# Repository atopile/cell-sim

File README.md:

# Cell Simulator

This cell-sim is designed to mimic a LiPo battery pack for development of surrounding electronics (e.g. a BMS).

- 16 channels
- Open-Source hardware design, you can embed onto your own HIL setup
- ⚡️ 0-4.5V and 0-500mA per channel
- DMM muxed to each channel for arbitrarily precise measurement
- Open-circuit (open-wire) simulation on each channel
- 📏 16bit ADC feedback for voltage and current
- 🔌 USB w/ Python software interface (+ 100MBit Ethernet + WiFi waiting for firmware support)

## Documentation

- **Electronics**: this README (see diagrams below)
- **Software (firmware + Python)**: `SOFTWARE.md`

## Design overview

## How it works (electronics)

### System-level overview

```mermaid
flowchart TB
  %% ----------------------------
  %% Power tree
  %% ----------------------------
  subgraph PWR["Power tree"]
    XT30["XT30 input<br/>12-20V"] --> PI["Pi filter"] --> ISENSE["Input current sensor"] --> VIN["POWER_IN<br/>12-20V rail"]
    VIN --> BUCK5["LV2842X buck<br/>12-20V to 5V"]
    USBC["USB-C"] -->|VBUS 5V| OR["Diode OR-ing"]
    BUCK5 --> OR --> P5V["5V rail"]
    P5V --> LDO33["LDK220 LDO<br/>5V to 3.3V"] --> P3V3["3.3V rail"]
  end

  %% ----------------------------
  %% Controller + comms
  %% ----------------------------
  subgraph MCU["Controller + comms"]
    ESP["ESP32-S3"]:::mcu
    P3V3 --> ESP
    USBC -->|USB2 data| ESP

    ESP -->|I2C bus #1| I2C1["I2C1"]
    ESP -->|I2C bus #2| I2C2["I2C2"]

    I2C1 --> MUX1["TCA9548A #1<br/>addr 0x70"]
    I2C2 --> MUX2["TCA9548A #2<br/>addr 0x70"]
    P3V3 --> MUX1
    P3V3 --> MUX2

    ESP -->|SPI| W5500["W5500 Ethernet<br/>hw present; fw WIP"]
    P3V3 --> W5500
  end

  %% ----------------------------
  %% 16 cell channels (stacked)
  %% ----------------------------
  subgraph STACK["16x isolated cell channels<br/>stacked like a battery pack"]
    direction TB
    C1["Cell #1<br/>pack GND reference"] --> C2["Cell #2"] --> C3["Cell #3"] --> C4["Cell #4"] --> C5["Cell #5"] --> C6["Cell #6"] --> C7["Cell #7"] --> C8["Cell #8"]
    C8 --> C9["Cell #9"] --> C10["Cell #10"] --> C11["Cell #11"] --> C12["Cell #12"] --> C13["Cell #13"] --> C14["Cell #14"] --> C15["Cell #15"] --> C16["Cell #16<br/>pack +"]
  end

  %% Per-cell services fed from global rails
  VIN -->|12-20V feed| STACK
  P5V -->|logic / relay / LED feed| STACK
  P3V3 -->|isolator side power| STACK

  %% I2C fanout
  MUX1 -->|ports 0-7 to cells 1-8| C1
  MUX2 -->|ports 0-7 to cells 9-16| C9

  %% ----------------------------
  %% DMM path (precision external measurement)
  %% ----------------------------
  subgraph DMM["External DMM measurement path"]
    BANANA["Banana jacks<br/>DMM connector"] --> DMMBUS["DMM_OUT bus"]

    ESP -->|S0..S3 + /EN| DMMSW["CD74HC4067<br/>16:1 mux"]
    P3V3 -->|3.3V select level| DMMSW
    DMMSW -->|CH0..CH15 -> per-cell dmm_relay_enable| STACK

    STACK -->|selected cell closes DMM relay, routes output to DMM_OUT| DMMBUS
  end

  %% ----------------------------
  %% Thermistor simulator
  %% ----------------------------
  subgraph THERM["4x digital thermistor simulator"]
    TSIM["Isolated thermistor simulator<br/>MCP4728 DAC + ADS1115 ADC"] -->|4 analog thermistor nodes| THOUT["thermistor outputs"]
    I2C2 -->|I2C control| TSIM
    VIN -->|12-20V| TSIM
    P3V3 -->|logic-side isolator power| TSIM
  end

  classDef mcu fill:#eef,stroke:#446;
```

### What a single cell channel does internally

Each channel is effectively an *isolated, digitally-controlled power supply* whose output is treated like a single LiPo cell. The channels are then wired in series to create a 16S “battery pack” at the output connector.

```mermaid
flowchart LR
  %% One "Cell" module from elec/src/cell.ato
  subgraph CELL["One cell channel<br/>isolated"]
    direction LR

    %% Power path (high-level)
    VIN["POWER_IN<br/>12-20V"] --> ISO_DCDC["Isolated DC/DC<br/>B1205S"] --> ISO5V["Isolated 5V"]
    ISO5V --> INTLDO["Local LDO<br/>5V to 3.3V"] --> ISO3V3["Isolated 3.3V<br/>logic"]

    ISO5V --> DBUCK["Digitally-controlled buck"] --> DLDO["Digitally-controlled LDO"] --> PF["Pi filter"] --> CS["Current sense"] --> OUTRELAY["Output relay"] --> VOUT["Cell output"]

    %% Control + monitoring (isolated I2C domain)
    I2C_IN["I2C from mux port"] --> ISOI2C["ISO1640 I2C isolator"] --> I2C_ISO["I2C isolated"]
    ISO3V3 --> ISOI2C

    I2C_ISO --> DACB["DAC @0x61<br/>buck setpoint"]
    I2C_ISO --> DACL["DAC @0x60<br/>LDO setpoint"]
    I2C_ISO --> ADC["ADS1115 @0x48<br/>telemetry"]
    I2C_ISO --> GPIO["TCA6408 @0x20<br/>GPIO expander"]
    I2C_ISO --> ISENSE_IC["Current sense IC @0x21"]

    GPIO -->|enable| DBUCK
    GPIO -->|enable| DLDO
    GPIO -->|control| LOADSW["Load switch"]
    GPIO -->|control| OUTRELAY

    %% Telemetry points
    ADC -->|buck V| DBUCK
    ADC -->|LDO V| DLDO
    ADC -->|output V| VOUT
    ADC -->|shunt V| CS

    %% Fast discharge path
    PF --> LOADSW --> RLOAD["Discharge resistor"] --> PF

    %% Precision measurement path (selected externally)
    CS --> DMMRELAY["DMM relay"] --> RLIM["Current-limiting resistors"] --> DMM_OUT["DMM_OUT bus"]
  end
```

## Getting Started

1. Install python if you don't have it already
2. Install the requirements `pip install -r requirements.txt`
3. Connect the board via USB

4. Power the board with the 12V input (supply: 1A minimum, 3A recommended)
5. Run the example python script `python example_set_voltages.py`
6. Voltages should be set to 3.5V, then rainbow from 1V to 4V across the 16 channels and current should be close to 0A.

You should see something like this:

## Notes
1. To get best low noise performance, use a quality power supply for the input supply.

## Manufacturing
Board is intended to be manufactured with JLC, files are in the main directory of the repository.
Note, the highlighted isolated regulator needs to be depopulated:

## Firmware

### Update Firmware
We use PlatformIO to build and upload the firmware via USB.
1. Install PlatformIO: https://platformio.org/install
2. Connect the board via USB (might need to accept connection popup on Mac)
3. Run `pio run -t upload` or install the PlatformIO VSCode extension and use the upload button.

See `SOFTWARE.md` for firmware architecture, protocol, and troubleshooting.

## API Docs
### Connecting to cellsim

```python
from lib.cellsim import CellSim
cellsim = CellSim(port)
```

### Enable outputs
Each cell has a relay in series between the cell output and the connector, this can be  used to simulate open-wire faults for example.

```python
# Global enable/disable
cellsim.enableOutputAll()
time.sleep(1)
cellsim.disableOutputAll()
time.sleep(1)

# Enable/disable one at a time
# Turn relays on in a wave
for i in range(1, 17):
    cellsim.enableOutput(i)
    time.sleep(0.1)

time.sleep(1)

# Turn relays off in a wave
for i in range(1, 17):
    cellsim.disableOutput(i)
    time.sleep(0.1)
```

### Setting voltages
Each output voltage can be specified between 0.5V and 4.4V

```python
# Set all at once
cellsim.setAllVoltages(3.5)
time.sleep(1)

# Set one at a time
print("\nSetting rainbow voltage pattern...")
for i in range(16):
    voltage = 1.0 + (3.0 * i / 15)  # Spread 1V to 4V across 16 channels
    cellsim.setVoltage(i + 1, voltage)
```

### Measuring voltages (onboard)
Each channel has an onboard 16bit ADC that measures the cell output. Note this is not a kelvin connection to your DUT, the measurement will only be accurate when minimal current is being drawn by the DUT.

```python
voltages = cellsim.getAllVoltages()
print(f"Voltages: {[f'{v:.3f}' for v in voltages]}")
```
  
### Measuring voltages externally
To take a precision measurement, each channel has a multiplexed output that connects to the DMM connector via a relay.

```python
channel_to_measure = 3
# Enable DMM
cellsim.enableDMM(channel_to_measure)

# take measurment using external DMM
# that is connected to the DMM banana outputs
time.sleep(1)

cellsim.disableDMM()
```

### Load switch
Each channel has a resistor + mosfet across its output, this can be used to speed up the discharge of the output capacitors. For example when transitioning from a high output voltage to a low output voltage, there will be an RC decay time before the voltage settles, typically in the ~100ms range. Turning on the load switch will make this much faster.

```python
cellsim.enableLoadSwitchAll()
time.sleep(1)

cellsim.disableLoadSwitchAll()
time.sleep(1)
```

### Disconnecting session
Once your test is finished, you can use the following to close the serial session:
```python
  cellsim.close()
```

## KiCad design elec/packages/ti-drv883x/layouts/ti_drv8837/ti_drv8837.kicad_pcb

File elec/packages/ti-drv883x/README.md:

# Texas Instruments DRV8837/DRV8838 H-Bridge Motor Drivers

Low-voltage H-bridge motor drivers for brushed DC motors.

- **DRV8837**: IN0/IN1 control interface
- **DRV8838**: PH/EN (Phase/Enable) control interface

## Features

- Logic voltage: 1.8V to 7V
- Motor voltage: 0V to 11V
- Integrated decoupling capacitors
- Sleep control for low-power mode

## Usage

```ato
#pragma experiment("TRAITS")
#pragma experiment("BRIDGE_CONNECT")
#pragma experiment("MODULE_TEMPLATING")

import ElectricPower
import ElectricLogic
import Electrical
import can_bridge_by_name

from "atopile/ti-drv883x/ti-drv883x.ato" import TI_DRV8837
from "atopile/ti-drv883x/ti-drv883x.ato" import TI_DRV8838

module FakeMotor:
    """
    Mock motor device for testing
    """
    unnamed = new Electrical[2]
    trait can_bridge_by_name<input_name = "unnamed[0]", output_name = "unnamed[1]">

module Usage:
    """
    Example usage of the TI_DRV8837 and TI_DRV8838 H-bridge (motor) drivers
    """

    power_3v3 = new ElectricPower
    power_3v3.voltage = 3.3V +/- 5%
    power_6v = new ElectricPower
    power_6v.voltage = 6V +/- 5%

    # some mock gpio from e.g. a gpio expander
    gpio_0 = new ElectricLogic
    gpio_1 = new ElectricLogic
    gpio_3 = new ElectricLogic

    motor_driver_in0_in1 = new TI_DRV8837
    motor_driver_in0_in1.logic_power ~ power_3v3
    motor_driver_in0_in1.motor_power ~ power_6v
    motor_driver_in0_in1.sleep ~ gpio_3
    motor_driver_in0_in1.inputs[0] ~ gpio_0
    motor_driver_in0_in1.inputs[1] ~ gpio_1
    motor_0 = new FakeMotor
    motor_driver_in0_in1.motor_outs[0] ~> motor_0 ~> motor_driver_in0_in1.motor_outs[1]

    motor_driver_ph_en = new TI_DRV8838
    motor_driver_ph_en.logic_power ~ power_3v3
    motor_driver_ph_en.motor_power ~ power_6v
    motor_driver_ph_en.sleep ~ gpio_3
    motor_driver_ph_en.phase ~ gpio_0
    motor_driver_ph_en.enable ~ gpio_1
    motor_1 = new FakeMotor
    motor_driver_ph_en.motor_outs[0] ~> motor_1 ~> motor_driver_ph_en.motor_outs[1]

```

### DRV8837 Truth Table (IN0/IN1)

| nSLEEP | IN1 | IN2 | OUT1 | OUT2 | Function |
| ------ | --- | --- | ---- | ---- | -------- |
| 0      | X   | X   | Z    | Z    | Coast    |
| 1      | 0   | 0   | Z    | Z    | Coast    |
| 1      | 0   | 1   | L    | H    | Reverse  |
| 1      | 1   | 0   | H    | L    | Forward  |
| 1      | 1   | 1   | L    | L    | Brake    |

### DRV8838 Truth Table (PH/EN)

| nSLEEP | PH  | EN  | OUT1 | OUT2 | Function |
| ------ | --- | --- | ---- | ---- | -------- |
| 0      | X   | X   | Z    | Z    | Coast    |
| 1      | X   | 0   | L    | L    | Brake    |
| 1      | 1   | 1   | L    | H    | Reverse  |
| 1      | 0   | 1   | H    | L    | Forward  |

## Contributing

Contributions to this package are welcome via pull requests on the GitHub repository.

## License

This atopile package is provided under the [MIT License](https://opensource.org/license/mit/).

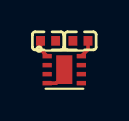
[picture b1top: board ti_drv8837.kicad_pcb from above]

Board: 2 copper layers, 3 parts (0 on the bottom side), 3 nets.

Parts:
C1, C2: 100nF; C0402
U1: WSON-8_L2.0-W2.0-P0.50-TL-EP

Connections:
hv: C1.1, U1.8
lv: C1.2, C2.2, U1.4, U1.9
motor_power_decoupling_capacitor-power-hv: C2.1, U1.1

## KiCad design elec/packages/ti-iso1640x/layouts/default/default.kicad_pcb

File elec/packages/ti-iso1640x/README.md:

# Texas Instruments ISO1640QDWRQ1 Bidirectional I2C Isolator

The ISO1640QDWRQ1 is a bidirectional I2C isolator that provides 1500V isolation between two I2C buses. It supports data rates up to 1MHz and operates with supply voltages from 2.25V to 5.5V on each side. This device is automotive qualified (AEC-Q100).

## Usage

```ato
import I2C
import ElectricPower

from "atopile/ti-iso1640x/ti-iso1640x.ato" import TI_ISO1640QDWRQ1

module Usage:
    """
    Example usage of ISO1640QDWRQ1 I2C isolator
    """

    isolator = new TI_ISO1640QDWRQ1

    power_3v3 = new ElectricPower
    power_iso_3v3 = new ElectricPower

    assert power_3v3.voltage within 3.3V +/- 5%
    assert power_iso_3v3.voltage within 3.3V +/- 5%

    i2c_mcu = new I2C
    i2c_sensor = new I2C

    assert i2c_mcu.frequency <= 400kHz
    assert i2c_sensor.frequency <= 400kHz

    # Connections
    i2c_mcu ~ isolator.i2cs[0]
    i2c_sensor ~ isolator.i2cs[1]
    power_3v3 ~ isolator.power_rails[0]
    power_iso_3v3 ~ isolator.power_rails[1]
```

## Contributing

Contributions are welcome! Feel free to open issues or pull requests.

## License

This package is provided under the [MIT License](https://opensource.org/license/mit/).

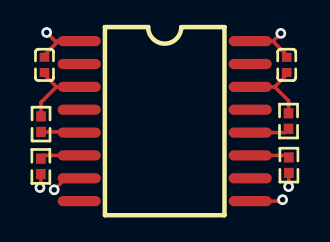
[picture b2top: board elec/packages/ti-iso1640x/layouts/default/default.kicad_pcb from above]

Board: 2 copper layers, 7 parts (0 on the bottom side), 6 nets.

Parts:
C1, C2: 100nF; C0402
R1, R2, R3, R4: 10kΩ; R0402
U1: SOIC-16_L10.3-W7.4-P1.27-LS10.3-BL

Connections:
SCL: R1.2, R2.2, U1.6, U1.11
SDA: R3.2, R4.2, U1.5, U1.12
decoupling_cap_side2-power-hv: C2.1, R2.1, R4.1, U1.14
decoupling_cap_side2-power-lv: C2.2, U1.9, U1.16
hv: C1.1, R1.1, R3.1, U1.3
lv: C1.2, U1.1, U1.7

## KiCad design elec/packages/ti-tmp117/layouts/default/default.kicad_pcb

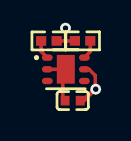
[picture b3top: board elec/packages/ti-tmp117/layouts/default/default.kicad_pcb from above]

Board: 2 copper layers, 4 parts (0 on the bottom side), 4 nets.

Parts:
C1: 100nF; C0402
R1, R2: 10kΩ; R0402
U1: WSON-6_L2.0-W2.0-P0.65-TL-EP

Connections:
SCL: R1.1, U1.1
SDA: R2.1, U1.6
hv: C1.1, R1.2, R2.2, U1.5
lv: C1.2, U1.2, U1.4, U1.7

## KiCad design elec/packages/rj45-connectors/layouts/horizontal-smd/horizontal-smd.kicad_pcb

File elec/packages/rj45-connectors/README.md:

# RJ45 Connectors

## Usage

```ato
#pragma experiment("BRIDGE_CONNECT")
#pragma experiment("FOR_LOOP")
#pragma experiment("TRAITS")

import Electrical
import ElectricLogic
import ElectricPower
import Ethernet

from "atopile/rj45-connectors/rj45-connectors.ato" import RJ45_Vertical_SMD
from "atopile/rj45-connectors/rj45-connectors.ato" import RJ45_Horizontal_TH_Magnetics
from "atopile/rj45-connectors/rj45-connectors.ato" import RJ45_Recessed_SMD
from "atopile/rj45-connectors/rj45-connectors.ato" import RJ45_Horizontal_TH_Magnetics_8Port
from "atopile/rj45-connectors/rj45-connectors.ato" import RJ45_Horizontal_SMD_Magnetics

module Usage:
    """
    Usage examples for RJ45 connectors package.

    Shows how to use both the vertical SMD connector (without magnetics)
    and the horizontal through-hole connector (with integrated magnetics).
    """

    # --- Power supply for logic references ---
    power_3v3 = new ElectricPower
    assert power_3v3.voltage within 3.3V +/- 5%

    # --- Example 1: Vertical SMD connector (no magnetics) ---
    rj45_vertical = new RJ45_Vertical_SMD

    # Connect Ethernet interface power reference
    rj45_vertical.ethernet.led_link.reference ~ power_3v3
    rj45_vertical.ethernet.led_speed.reference ~ power_3v3

    # Connect shield to ground
    rj45_vertical.shield ~ power_3v3.lv

    # --- Example 2: Horizontal TH connector with magnetics ---
    rj45_horizontal = new RJ45_Horizontal_TH_Magnetics

    # Connect Ethernet interface power reference
    rj45_horizontal.ethernet.led_link.reference ~ power_3v3
    rj45_horizontal.ethernet.led_speed.reference ~ power_3v3

    # Connect shield to ground
    rj45_horizontal.shield ~ power_3v3.lv

    # --- Example 3: Horizontal SMD connector with magnetics (HCTL HC632701A-M906-A) ---
    rj45_horizontal_smd = new RJ45_Horizontal_SMD_Magnetics
    rj45_horizontal_smd.ethernet.led_link.reference ~ power_3v3
    rj45_horizontal_smd.ethernet.led_speed.reference ~ power_3v3
    rj45_horizontal_smd.shield ~ power_3v3.lv

    # --- Example connections to external circuits ---
    # For the magnetics connector, you can connect directly to an Ethernet PHY:
    # phy.ethernet ~ rj45_horizontal.ethernet
    # For the vertical SMD, you would typically need external transformers

    rj45_recessed = new RJ45_Recessed_SMD
    rj45_recessed.ethernet.led_link.reference ~ power_3v3
    rj45_recessed.ethernet.led_speed.reference ~ power_3v3

    # Connect shield to ground
    rj45_recessed.shield ~ power_3v3.lv

    rj45_8port = new RJ45_Horizontal_TH_Magnetics_8Port
    # Connect shield to ground
    rj45_8port.shield ~ power_3v3.lv
```

## Contributing

Contributions are welcome! Feel free to open issues or pull requests.

## License

This package is provided under the [MIT License](https://opensource.org/license/mit).

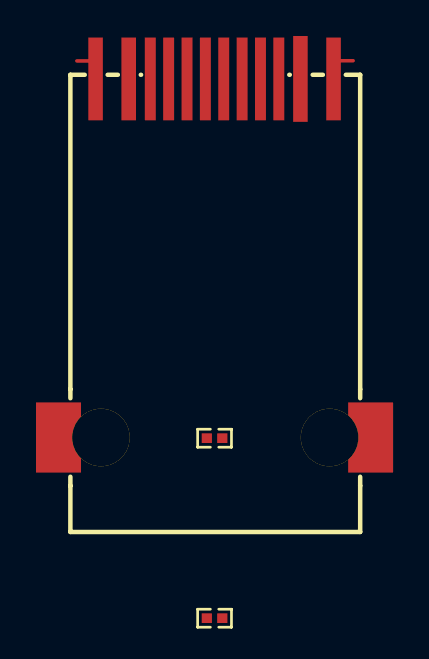
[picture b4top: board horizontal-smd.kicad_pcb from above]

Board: 2 copper layers, 3 parts (0 on the bottom side), 4 nets.

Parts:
R1, R2: 470Ω; R0402
RJ1: RJ45-SMD_BS-R250210

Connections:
CT: RJ1.3, RJ1.4
L_LED_Gpos: R2.2, RJ1.12
R_LEDYpos: R1.2, RJ1.9
lv: RJ1.8, RJ1.10, RJ1.11, RJ1.13, RJ1.14

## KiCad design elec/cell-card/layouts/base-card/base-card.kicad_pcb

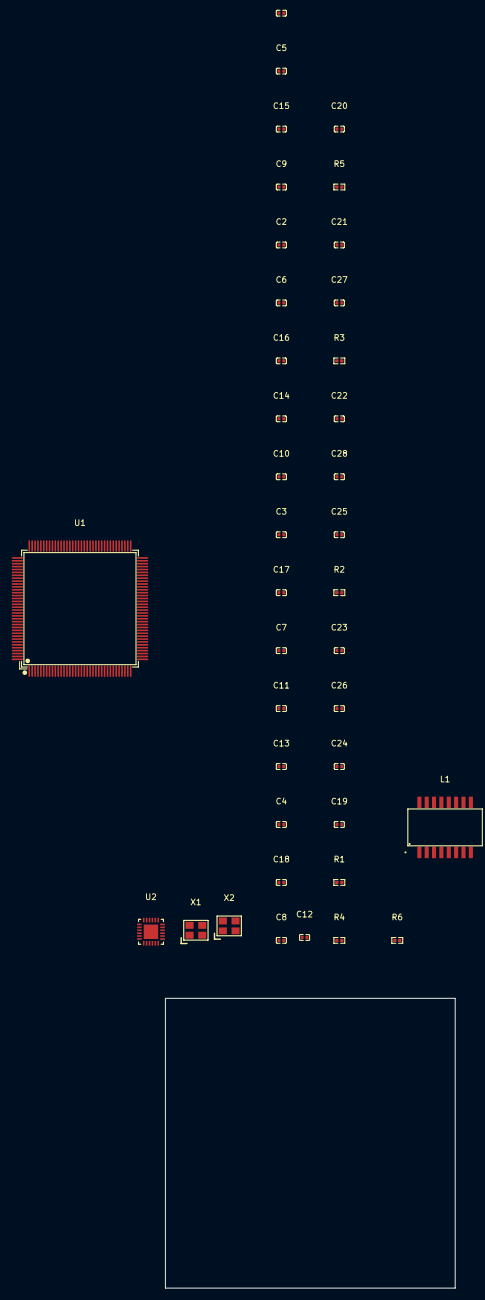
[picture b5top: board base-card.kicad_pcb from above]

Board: 2 copper layers, 50.0 x 50.0 mm, 39 parts (0 on the bottom side), 27 nets, no tracks yet.

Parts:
C1, C2, C3, C4, C5, C6, C7, C8, C9, C10, C11, C12, C18, C19, C20, C21, C22, C23: 100nF; C0402
C13, C14, C27, C28: 18pF; C0402
C15, C16: 2.2µF; C0402
C17, C24, C25: 1µF; C0402
C26: 470pF; C0402
L1: SMD-16_L12.7-W7.2-P1.27-LS9.5-BL
R1, R2: 49.9Ω; R0402
R3, R5: 100kΩ; R0402
R4: 12.1kΩ; R0402
R6: 10kΩ; R0402
U1: LQFP-144_L20.0-W20.0-P0.50-LS22.0-BL
U2: QFN-24_L4.0-W4.0-P0.50-TL-EP2.5
X1, X2: OSC-SMD_4P-L3.2-W2.5-BL_SIT8008BI

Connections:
ETH_LED_LINK: R5.1, U2.3
MDC: U1.42, U2.13
RBIAS: R4.1, U2.24
RTC: L1.7, R1.1
TCT: L1.2, R2.1
TXEN: U1.70, U2.16
XIN: C13.1, U1.23, X1.1
XOUT: C14.1, U1.24, X1.3
ethernet-ETH_N0_N: L1.8, U2.22
ethernet-ETH_N1_N: L1.3, U2.20
ethernet-ETH_P0_P: L1.6, U2.23
ethernet-ETH_P1_P: L1.1, U2.21
hv: C19.1, L1.10, L1.15
line: U1.43, U2.11, U2.12
lv: C1.2, C2.2, C3.2, C4.2, C5.2, C6.2, C7.2, C8.2, C9.2, C10.2, C11.2, C12.2, C13.2, C14.2, C15.2, C16.2, C17.2, C18.2, C19.2, C20.2, C21.2, C22.2, C23.2, C24.2, C25.2, C26.2, C27.2, C28.2, R3.2, R4.2, R5.2, U1.16, U1.31, U1.38, U1.51, U1.61, U1.83, U1.94, U1.107, U1.120, U1.130, U2.25, X1.2, X1.4, X2.2, X2.4
nINT_REFCLKO: U1.35, U2.14
nRST: R6.1, U1.40, U2.15
phy-rmii-line: R3.1, U1.69, U2.10
phy-rmii-line-1: U1.73, U2.17
phy-rmii-line-2: U1.74, U2.18
phy-rmii-line-3: U1.44, U2.8
phy-rmii-line-4: U1.45, U2.7
vcap_caps[1]-power-hv: C15.1, C16.1, U1.71, U1.106
vddcr_caps[1]-power-hv: C25.1, C26.1, U2.6
vref_caps[1]-power-hv: C1.1, C2.1, C3.1, C4.1, C5.1, C6.1, C7.1, C8.1, C9.1, C10.1, C11.1, C12.1, C17.1, C18.1, C20.1, C21.1, C22.1, C23.1, C24.1, R1.2, R2.2, R6.2, U1.17, U1.30, U1.32, U1.33, U1.39, U1.52, U1.62, U1.72, U1.84, U1.95, U1.108, U1.121, U1.131, U1.144, U2.1, U2.9, U2.19
xtal_caps[0]-power-hv: C27.1, U2.5, X2.1
xtal_caps[1]-power-hv: C28.1, U2.4, X2.3

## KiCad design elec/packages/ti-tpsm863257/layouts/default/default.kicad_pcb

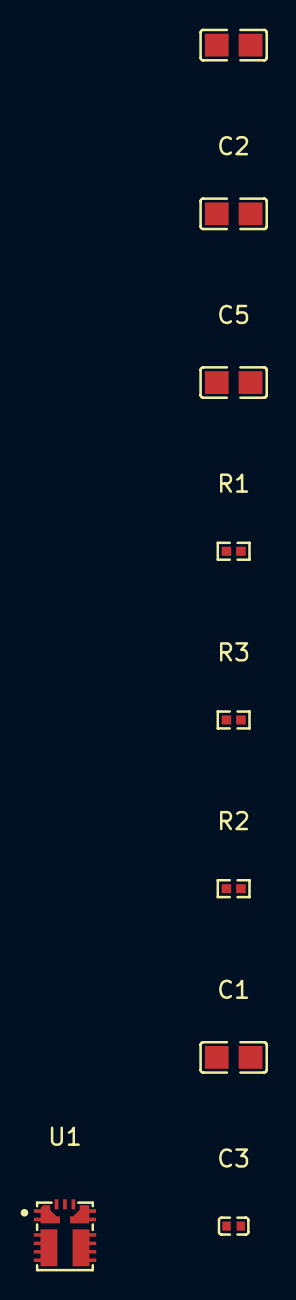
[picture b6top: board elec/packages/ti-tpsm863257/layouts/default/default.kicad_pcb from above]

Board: 2 copper layers, 9 parts (0 on the bottom side), 5 nets, no tracks yet.

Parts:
C1, C2: 10µF; C0805
C3: 100nF; C0402
C4, C5: 22µF; C0805
R1: 10kΩ; R0402
R2: 100kΩ; R0402
R3: 73.2kΩ; R0402
U1: QFN-7_L4.0-W3.3_TPSM863257RDXR

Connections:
FB: R1.1, R3.2, U1.7
PG: R2.2, U1.5
c_out[1]-power-hv: C4.1, C5.1, R2.1, R3.1, U1.3
hv: C1.1, C2.1, C3.1, U1.1
lv: C1.2, C2.2, C3.2, C4.2, C5.2, R1.2, U1.4

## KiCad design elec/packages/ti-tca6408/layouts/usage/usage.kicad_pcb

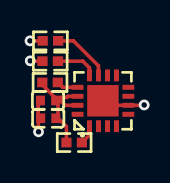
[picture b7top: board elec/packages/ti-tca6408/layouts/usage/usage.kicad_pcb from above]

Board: 2 copper layers, 7 parts (0 on the bottom side), 6 nets.

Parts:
C1, C2: 100nF; C0402
R1, R2, R3, R4: 4.7kΩ; R0402
U1: QFN-16_L3.0-W3.0-P0.50-BL-EP1.7

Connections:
SCL: R2.1, U1.12
SDA: R3.1, U1.13
hv: C1.1, C2.1, R1.1, R2.2, R3.2, R4.1, U1.14, U1.15
lv: C1.2, C2.2, U1.6, U1.17
nINT: R1.2, U1.11
nRESET: R4.2, U1.1

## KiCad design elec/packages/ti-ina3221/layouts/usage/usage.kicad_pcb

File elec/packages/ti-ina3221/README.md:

# Texas Instruments INA3221 Triple-Channel Current & Power Monitor

The INA3221 is a triple-channel, high-side current and power monitor with an I2C and SMBus-compatible interface from Texas Instruments. This device is ideal for monitoring multiple power rails in battery-powered systems, servers, and other applications requiring precise current measurement.

## Features

- **Triple-channel high-side current sensing**
- **Wide supply voltage range**: 2.7V to 5.5V (IC supply)
- **Bus voltage monitoring**: 0V to 26V per channel
- **High accuracy**: ±0.1% gain error (typical)
- **I2C interface** with configurable address (0x40-0x43)
- **Programmable conversion times** and averaging modes
- **Alert functionality** with warning and critical thresholds
- **Low power consumption**: 350µA typical supply current
- **Operating temperature**: -40°C to +125°C
- **16-bit ADC** with programmable conversion time
- **Compact package**: QFN-16 (4mm × 4mm)

## Usage

```ato
#pragma experiment("TRAITS")
#pragma experiment("BRIDGE_CONNECT")

import ElectricPower
import I2C
import has_part_removed

from "atopile/ti-ina3221/ti-ina3221.ato" import TI_INA3221

module Sink:
    """
    mock sink device for testing
    """
    power = new ElectricPower
    trait has_part_removed

module Usage:
    """
    Minimal usage example for TI INA3221 triple-channel current and power monitor.
    Shows how to connect power supply, I2C bus, and three monitored power rails.
    """

    # Create current monitor instance
    current_monitor = new TI_INA3221
    sinks = new Sink[3]

    # Main power supply for the IC (3.3V or 5V)
    power_3v3 = new ElectricPower
    power_3v3.voltage = 3.3V +/- 5%

    # External I2C bus
    i2c_bus = new I2C

    # Example monitored power rails
    power_5v = new ElectricPower
    power_5v.voltage = 5V +/- 5%

    # Connect interfaces
    power_3v3 ~ current_monitor.power
    i2c_bus ~ current_monitor.i2c

    # Connect monitored channels (bridgeable)
    power_5v ~> current_monitor.channels[0] ~> sinks[0].power
    power_5v ~> current_monitor.channels[1] ~> sinks[1].power
    power_5v ~> current_monitor.channels[2] ~> sinks[2].power

    # Set I2C address (default 0x40 with A0 pin low)
    current_monitor.i2c.address = 0x40

```

## Technical Specifications

- **Supply Voltage (VS)**: 2.7V to 5.5V
- **Bus Voltage Range**: 0V to 26V per channel
- **Common-Mode Voltage**: 0V to 26V
- **I2C Address**: 0x40 (default), 0x41, 0x42, 0x43 (configurable via A0 pin)
- **Supply Current**: 350µA (typical)
- **Shunt Voltage Range**: ±163.8mV
- **ADC Resolution**: 16-bit (13-bit effective)
- **Conversion Time**: 140µs to 8.244ms (programmable)
- **I2C Speed**: Up to 2.94 MHz
- **Package**: QFN-16 (4mm × 4mm)

## I2C Address Configuration

The INA3221 supports four different I2C addresses controlled by the A0 pin:

| A0 Connection | I2C Address | Description |
|---------------|-------------|-------------|
| GND           | 0x40        | Default configuration |
| VS            | 0x41        | Connected to supply voltage |
| SDA           | 0x42        | Connected to I2C data line |
| SCL           | 0x43        | Connected to I2C clock line |

## Pin Configuration

| Pin | Name      | Description |
|-----|-----------|-------------|
| 1   | IN_3      | Channel 3 Input (-) |
| 2   | INplus3   | Channel 3 Input (+) |
| 3   | GND       | Ground |
| 4   | VS        | Supply Voltage |
| 5   | A0        | Address Select Pin |
| 6   | SCL       | I2C Serial Clock |
| 7   | SDA       | I2C Serial Data |
| 8   | WARNING   | Warning Alert Output |
| 9   | CRITICAL  | Critical Alert Output |
| 10  | PV        | Pullup Voltage |
| 11  | IN_1      | Channel 1 Input (-) |
| 12  | INplus1   | Channel 1 Input (+) |
| 13  | TC        | Timing Control |
| 14  | IN_2      | Channel 2 Input (-) |
| 15  | INplus2   | Channel 2 Input (+) |
| 16  | VPU       | Internal Pullup |
| 17  | PAD       | Exposed Pad (Ground) |

## Current Sensing Configuration

The INA3221 includes three `Channel` modules, each with integrated shunt resistors:

### Channel Module Features
- **Bridgeable design**: Use `~>` to connect power rails through the current sensor
- **Integrated shunt resistor**: Default 100mΩ ±1% (configurable)
- **Power flow**: `power_in ~> shunt ~> power_out`
- **Differential sensing**: Connected to INA3221 via `sense.p` and `sense.n`
- **Bus voltage monitoring**: 0V to 26V per channel

### Shunt Resistor Selection
- **Shunt voltage range**: ±163.8mV
- **Typical shunt values**: 0.1Ω, 0.01Ω, 0.001Ω
- **Current calculation**: I = V_shunt / R_shunt
- **Power calculation**: P = V_bus × I

### Example Usage Patterns
```ato
# Direct monitoring (channel as bridge)
power_source ~> current_monitor.channels[0] ~> load

# Monitoring without load connection
power_rail ~ current_monitor.channels[1].power_in
# Load connects to channels[1].power_out separately
```

## Applications

- Battery management systems
- Server and datacenter power monitoring
- Industrial automation
- Automotive power management
- Solar power systems
- Multi-rail power supplies
- IoT device power profiling
- Power consumption analysis

## Alert Functions

- **WARNING**: Configurable threshold for bus voltage, shunt voltage, or power
- **CRITICAL**: Configurable threshold for bus voltage, shunt voltage, or power
- **Timing Control**: External conversion triggering
- **Conversion-ready flag**: Available via I2C status register

## Contributing

Contributions are welcome! Feel free to open issues or pull requests.

## License

This package is provided under the [MIT License](https://opensource.org/license/mit).

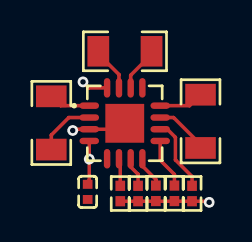
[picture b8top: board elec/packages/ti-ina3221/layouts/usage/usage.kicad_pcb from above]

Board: 2 copper layers, 10 parts (0 on the bottom side), 11 nets.

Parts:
C1: 100nF; C0402
R1, R2, R6, R7, R8: 10kΩ; R0402
R3, R4, R5: 150mΩ; R1206
U1: QFN-16_L4.0-W4.0-P0.65-TL-EP2.2

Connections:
CRITICAL: R6.2, U1.9
PV: R7.2, U1.10
SCL: R1.2, U1.6
SDA: R2.2, U1.7
WARNING: R8.2, U1.8
hv: C1.1, R1.1, R2.1, R6.1, R7.1, R8.1, U1.4, U1.16
lv: C1.2, U1.3, U1.5, U1.17
power_5v_P: R3.1, R4.1, R5.1, U1.2, U1.12, U1.15
power_N: R3.2, U1.11
sinks[1]-power-power_N: R4.2, U1.14
sinks[2]-power-power_N: R5.2, U1.1

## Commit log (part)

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2025-05-07 fix current rounding issue
2025-08-19 add check for input voltage to be within valid range before calibrating
2025-08-19 add fast calibrate
2025-08-19 make startup sequence smoother
2025-11-25 Update README with CellSim API documentation
    Added API documentation for CellSim functionality including enabling outputs, setting voltages, measuring voltages, and using load switch.
2026-01-20 exclude llm ad ai files
2026-01-20 remove random files
2026-01-20 remove deprecated footprint folder
2026-01-21 wip update packages and ato code, delete generics and use std lib, update package deps
2026-01-26 update and add last modules
2026-02-11 update documentation a bit
2026-02-11 update deps
2026-02-26 Add manufacturing section to README
    Added manufacturing instructions and a note about the isolated regulator.
2026-02-26 Update README with manufacturing instructions
    Added note about depopulating the isolated regulator during manufacturing.
2026-02-27 cellsimv2 cleanup
2026-02-28 progress
2026-02-28 Cleanup
2026-03-11 adhd commit
2026-04-09 Wip ato 0.15.3 compatibility
